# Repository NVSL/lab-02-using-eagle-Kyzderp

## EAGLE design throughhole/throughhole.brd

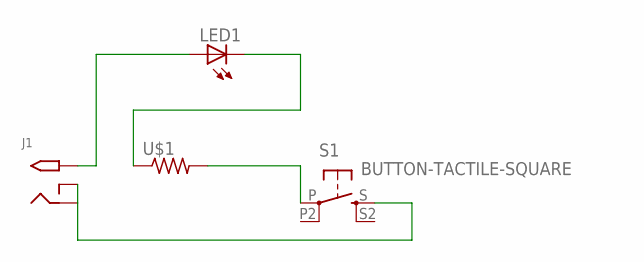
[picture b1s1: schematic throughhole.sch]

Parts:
J1: 2.1MMJACKTHM; PJ-102A
LED1: LED5MM
S1: BUTTON-TACTILE-SQUARE; BUTTON-TACTILE-SQUARE-ADAFRUIT1010
U$1: RESISTORTH-1/4W-CARBON; RESAD1160W55L680D260_HS

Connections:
unnamed: S1.P, U$1.2
unnamed: LED1.K (C), U$1.1
unnamed: J1.TIP, LED1.A
unnamed: J1.RING, J1.RING_SW, S1.S

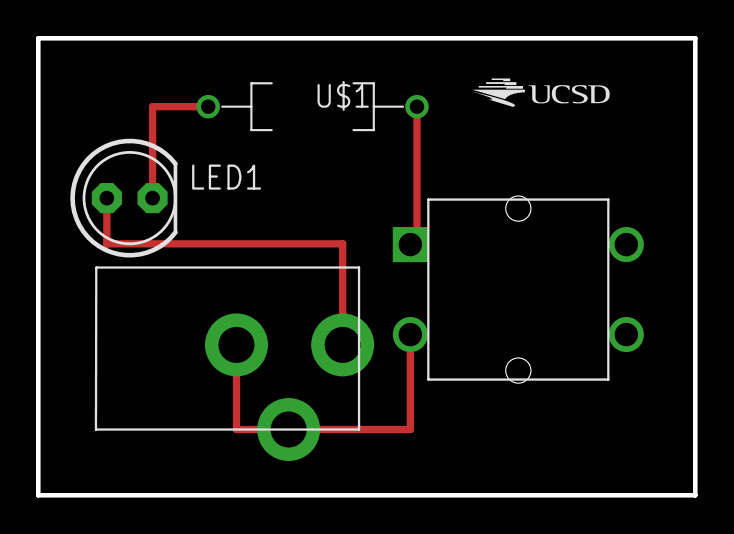
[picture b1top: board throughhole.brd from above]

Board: 2 copper layers, 36.5 x 25.4 mm, 5 parts (0 on the bottom side), 4 nets.

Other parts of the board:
U$2: UCSD_LOGO

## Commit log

2016-04-07 wheee time for bed
